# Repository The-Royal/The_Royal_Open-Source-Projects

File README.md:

# The_Royal_Projects
 **A Master Repository For All things Royal Made.**

 From Here forward, all complete, public, and open-sourced projects of my own design will be found here within this repository for consistency and clarity. 

---

 ## Thank You To Everyone for Making these projects possible!

- I’m always down for a nice coffee, beer, or cup of tea. 
- Click my Buymeacoffee link below if you wanted to make a small tip donation <3
- Even just these little donation are so, very much, appreciated.  These really Help me to keep these little projects going and to keep them open source for you guys. 

---

# ***Project Tables:***

## **.01 - Complete Kits**

| *Project* | *Excerpt* | *Main Files for Download* | *Featured Image* |
| --- | --- | :---: | :---: |
| [The Ave.](https://github.com/The-Royal/The_Royal_Open-Source-Projects/tree/master/01%20-%20Complete%20Kits/The_Ave-rev1.2) | A Mighty 50% Battlestation | PCB, Gerbers, Case STLs, RAW CAD |  |
| [LittleFoot](https://github.com/The-Royal/The_Royal_Open-Source-Projects/tree/master/01%20-%20Complete%20Kits/The_Little_Foot-Keyboard-rev2.3) | A Mighty Small, 45% Keyboard  | PCB, Gerbers, Case STLs, RAW CAD |  |
| [RoMac2.1](https://github.com/The-Royal/The_Royal_Open-Source-Projects/tree/master/01%20-%20Complete%20Kits/The_RoMac_rev2.1) | A “Plaid” Keyboard Inspired Macropad | PCB, Gerbers, Acrylic Cover, Diode Tool |  |

## **.02 - PCBs**

| *Project* | *Excerpt* | *Main Files for Download* | *Featured Image* |
| --- | --- | :---: | :---: |
| [Schwann](https://github.com/The-Royal/The_Royal_Open-Source-Projects/tree/schwann/02%20-%20PCBs/Schwann_PCB) | An Ortholinear *"HHKB-Style"* PCB | PCB Gerbers, Plates |  |

## **.03 - Cases**
| *Project* | *Excerpt* | *Main Files for Download* | *Featured Image* |
| --- | --- | :---: | :---: |
| [Minivan 3DP Case](https://github.com/The-Royal/The_Royal_Open-Source-Projects/tree/master/03%20-%20Cases/Minivan%203D%20Printed%20Case) | A Simple Minivan Case | STLs |  |
| [Minivan FR4 Plate Case](https://github.com/The-Royal/The_Royal_Open-Source-Projects/tree/master/03%20-%20Cases/Minivan%20Plate%20Case) | A 2-Part FR4(PCB Material) Plate Case for (rev3+) Minivan PCBs | Gerbers |  |
| [*Vitamins Inc.* Case](https://github.com/The-Royal/The_Royal_Open-Source-Projects/tree/master/03%20-%20Cases/Vitamins-Included_Case-master) | A 3D-Printed Case for the Hotswap Ed. Let's Split Keyboard | Case STLs, Plates |  |

## **.04 - FR4 Plates**
| *Switch Plate* | *Material* | *Main Files for Download* | *Featured Image* |
| --- | --- | :---: | :---: |
| [Minivan FR4 Plates](https://github.com/The-Royal/The_Royal_Open-Source-Projects/tree/master/04%20-%20FR4%20Plates/FR4_Plate-Minivan) | FR4 *(PCB Material)* | Gerbers |  |
| [Roadkit FR4 Plates](https://github.com/The-Royal/The_Royal_Open-Source-Projects/tree/master/04%20-%20FR4%20Plates/FR4_Plate-Roadkit) | FR4 *(PCB Material)* | Gerbers |  |

## **.05 - Other**
| *Project* | *Excerpt* | *Main Files for Download* | *Featured Image* |
| --- | --- | :---: | :---: |
| [Spring Lube Station](https://github.com/The-Royal/The_Royal_Open-Source-Projects/tree/master/05%20-%20Other/Tools-Spring_Lube_Station) | A 3D-Printed Tool For More Consistent Switch-Spring Lubing  | STLs, Sketches |  |
| [Stem-A-Jig](https://github.com/The-Royal/The_Royal_Open-Source-Projects/tree/master/05%20-%20Other/Tools-Stem-a-Jig) | A 3D-Printed Stem Gripper For Hand Lubing Switch Stems **(designed around compliant mechanisms)* | STL, G-Code |  |

---

 ## Thank You *AGAIN* for Making These Projects Possible!

- I’m always down for a nice coffee, beer, or cup of tea. 
- Click my Buymeacoffee link below if you wanted to make a small tip donation <3
- Even just these little donation are so, very much, appreciated.  These really Help me to keep these little projects going and to keep them open source for you guys. 

---

```</end>```

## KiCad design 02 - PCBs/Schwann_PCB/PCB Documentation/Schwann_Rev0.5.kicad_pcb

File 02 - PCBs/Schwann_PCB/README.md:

# The Schwann PCB
## ```Updated Aug. 22, 2020: (rev0.5b) - "Added Dual RESET switch footprints (top/bottom)"```

An ortholinear "HHKB" style PCB.  Specifically designed for use in the [Neuron 40% Keyboard](https://geekhack.org/index.php?topic=102681.0) by Walletburner of Geekhack. 

While not proprietary, the Schwann PCB has cut-off bottom corners and may not be compatible with many, current, after-market cases.  A Custom Designed case will most likely be the correct route. Acrylic is always a solid option.

## **Specs/Features**
- Powered By QMK Firmware (*Soon to be in QMK Configurator)
- Compatible and Designed for use with the Neuron Keyboard Case
- USB Type-C Connection
- x8 Optional WS2812B RGB LEDs
- No In-Switch LED Support
- Expansive Ortholinear Bottom Row Options
- and (IMO) A Beautiful PCB Aesthetically

## [**Non-Official QMK Firmware Documentation Can Be Found Here**](https://github.com/TheRoyalSweatshirt/The_Royal_QMK_Firmware_Vault/tree/master/In-Development_Boards/schwann)

## **Layout Options**

## **Building**
This Repo was realeased to the public so that you can order some of these for yourself and skip the chain! Just upload the gerbers from the latest release section and send them to your favorite PCB Production facility ([JLCPCB](https://jlcpcb.com/) is a fantastic and Cheap Facility), Order the Components Listed below (My Personal Choice is [LCSC](https://lcsc.com/)), and solder up! 

*Thin Liquid Flux, Thin (.6mm Min Diameter) Solder, A Decent Soldering Iron/Station are required for a well function PCB and an intact sanity.

I am not responsible for anything DIY assembly you man do yourself.  This information is public so it is  between you and the PCB to decide who will be the victor.  Assemble safely and assemble confidently my friends!

## **Bill of materials (BOM)**
Amount is for a **SINGLE SCHWANN PCB**.

Multiply as needed for higher quantities.

| LCSC part # | Description   | Value   | Package  | Amount |
| ----------- | ------------- | ------- | -------- | ------:|
| C128353     | Capacitor     | 0.1uF   | 0805     | 3      |
| C215803     | Capacitor     | 1uF     | 0805     | 1      |
| C2099       | Diode         |         | SOD-123  | 48     |
| C20799      | Fuse          |         | 1206     | 1      |
| C165948     | USB Connector |         | SMD/THT  | 1      |
| C103904     | Resistor      | 10K     | 0805     | 2      |
| C147798     | Resistor      | 5.1K    | 0805     | 2      |
| C325772     | Resistor      | 22      | 0805     | 2      |
| C45874      | MCU           | 32U4-AU | QFN-44   | 1      |
| C32180      | Crystal       | 16MHz   | SMD-3213 | 1      |
| C127478     | RST_Switch    |         | SMD      | 1      |

***Optional/Other:**
| LCSC part # | Description   | Value   | Package  | Amount |
| ----------- | ------------- | ------- | -------- | ------:|
| C114585     | WS2812B       | RGB     | 5050     | 8      |

### **Note On Viewing PCB Documentation:*
The latest KiCAD version will be needed to view the PCB Docs.  As well as correct project file path configurations.

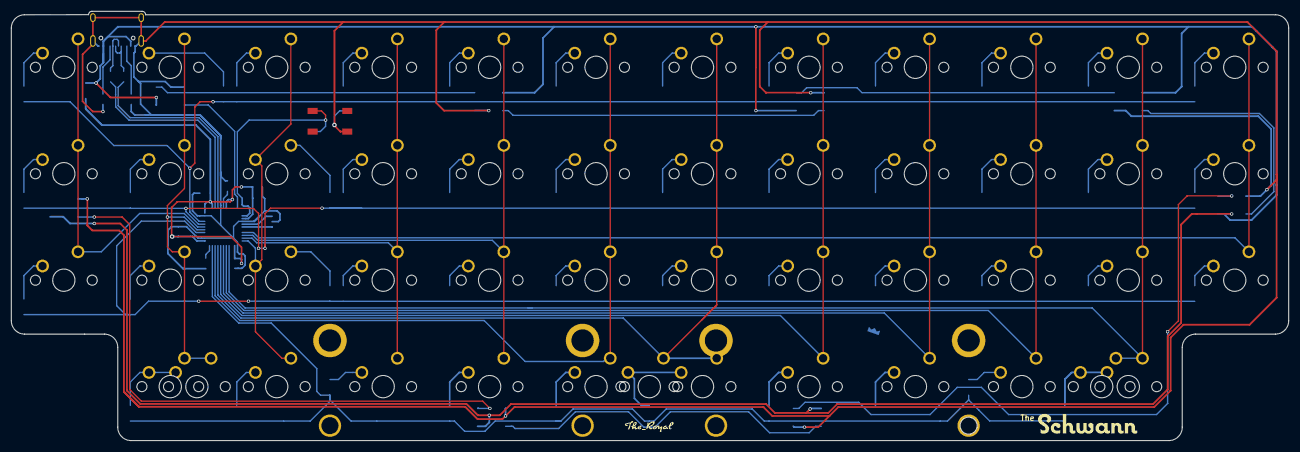
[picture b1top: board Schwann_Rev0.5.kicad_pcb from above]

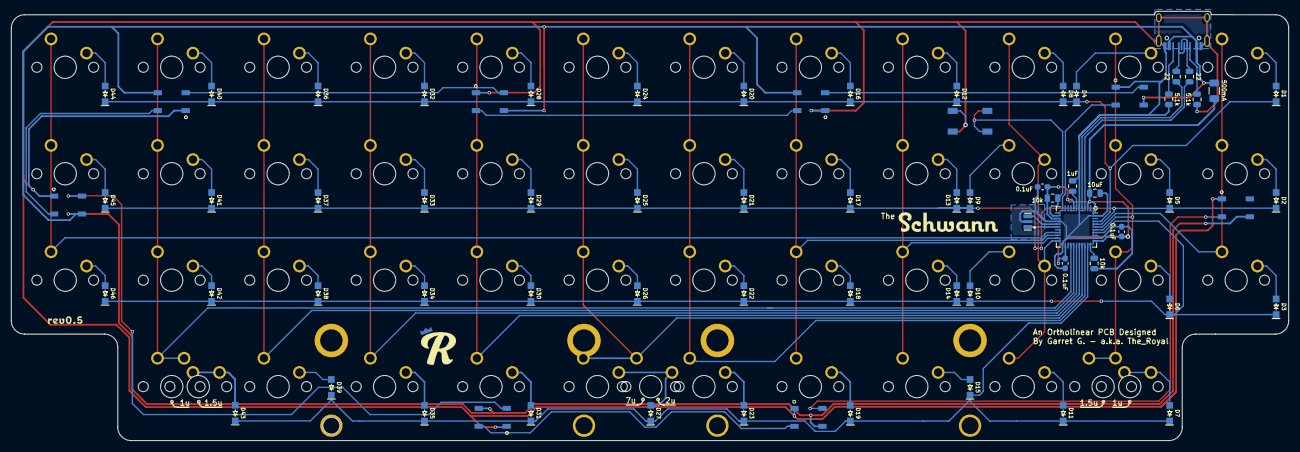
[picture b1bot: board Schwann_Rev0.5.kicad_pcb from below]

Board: 2 copper layers, 228.6 x 76.8 mm, 122 parts (70 on the bottom side), 84 nets.

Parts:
0.1uF, 0.1uF#2, 0.1uF#3: 0.1uF; C_0603_1608Metric_Pad1.05x0.95mm_HandSolder
1uF: 1uF; C_0805_2012Metric
5.1k, 5.1k#2: 5.1k; R_0805_2012Metric
10k, 10k#2: 10k; R_0805_2012Metric
10uF: 10uF; C_0805_2012Metric
22, 22#2: 22; R_0805_2012Metric
500mA: 500mA; Fuse_1206_3216Metric
Cystal1: CSTCE16M0V53-R0; CSTCE-V
D1, D2, D3, D4, D5, D6, D7, D8, D9, D10, D11, D12, D13, D14, D15, D16, D17, D18, D19, D20, D21, D22, D23, D24, D25, D26, D27, D28, D29, D30, D31, D32, D33, D34, D35, D36, D37, D38, D39, D40, D41, D42, D43, D44, D45, D46: D; D_SOD123_Basic
K7u1: KEYSW; MX_PCB_7u_STABONLY
KR2u1: KEYSW; MX_PCB_2u_STABONLY
MCU1: ATmega32U4-AU; QFN-44-1EP_7x7mm_P0.5mm_EP5.2x5.2mm
MX1, MX2, MX3, MX4, MX5, MX6, MX7, MX8, MX9, MX10, MX11, MX12, MX13, MX14, MX15, MX16, MX17, MX18, MX19, MX20, MX21, MX22, MX23, MX24, MX25, MX26, MX27, MX28, MX29, MX30, MX31, MX32, MX33, MX34, MX35, MX36, MX37, MX38, MX39, MX40, MX41, MX42, MX43, MX44, MX45, MX46: MX-NoLED; MX_PCB_100H_SIMPLE_NOSILK
MX1.5uL1, MX1.5uR1: MX-NoLED; MX_PCB_150H
MX_7u1: MX-NoLED; MX_PCB_100H_SIMPLE_NOSILK
RGB1, RGB2, RGB3, RGB4, RGB5, RGB7, RGB8, RGB10: WS2812B
Rst1, Rst1#2: SW_PUSH; SKQG-1155865
USB1: HRO-TYPE-C-31-M-12

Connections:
+5V: 0.1uF.1, 0.1uF#2.1, 0.1uF#3.1, 10k.1, 10uF.1, 500mA.1, MCU1.2, MCU1.7, MCU1.14, MCU1.24, MCU1.34, MCU1.44
D+: 22.2, USB1.6, USB1.8
D-: 22#2.2, USB1.5, USB1.7
GND: 0.1uF.2, 0.1uF#2.2, 0.1uF#3.2, 1uF.2, 5.1k.2, 5.1k#2.2, 10k#2.2, 10uF.2, Cystal1.2, MCU1.5, MCU1.15, MCU1.23, MCU1.35, MCU1.43, RGB1.3, RGB2.3, RGB3.3, RGB4.3, RGB5.3, RGB7.3, RGB8.3, RGB10.3, Rst1.1, Rst1#2.1, USB1.1, USB1.12, USB1.13
unnamed: 1uF.1, MCU1.6
unnamed: Cystal1.1, MCU1.17
unnamed: Cystal1.3, MCU1.16
unnamed: D1.2, MX1.2
unnamed: D2.2, MX13.2
unnamed: D3.2, MX25.2
unnamed: D4.2, MX2.2
unnamed: D5.2, MX14.2
unnamed: D6.2, MX26.2
unnamed: D7.2, MX1.5uL1.2, MX37.2
unnamed: D8.2, MX3.2
unnamed: D9.2, MX15.1
unnamed: D10.2, MX27.1
unnamed: D11.2, MX38.2
unnamed: D12.2, MX4.2
unnamed: D13.2, MX16.2
unnamed: D14.2, MX28.2
unnamed: D15.2, MX39.2
unnamed: D16.2, MX5.2
unnamed: D17.2, MX17.2
unnamed: D18.2, MX29.2
unnamed: D19.2, MX40.2
unnamed: D20.2, MX6.2
unnamed: D21.2, MX18.2
unnamed: D22.2, MX30.2
unnamed: D23.2, MX41.2
unnamed: D24.2, MX7.2
unnamed: D25.2, MX19.2
unnamed: D26.2, MX31.2
unnamed: D27.2, MX42.2, MX_7u1.2
unnamed: D28.2, MX8.2
unnamed: D29.2, MX20.2
unnamed: D30.2, MX32.2
unnamed: D31.2, MX43.2
unnamed: D32.2, MX9.2
unnamed: D33.2, MX21.2
unnamed: D34.2, MX33.2
unnamed: D35.2, MX44.2
unnamed: D36.2, MX10.2
unnamed: D37.2, MX22.2
unnamed: D38.2, MX34.2
unnamed: D39.2, MX45.2
unnamed: D40.2, MX11.2
unnamed: D41.2, MX23.2
unnamed: D42.2, MX35.2
unnamed: D43.2, MX1.5uR1.2, MX46.2
unnamed: D44.2, MX12.2
unnamed: D45.2, MX24.2
unnamed: D46.2, MX36.2
unnamed: 22#2.1, MCU1.3
unnamed: 22.1, MCU1.4
unnamed: 10k.2, MCU1.13, Rst1.2, Rst1#2.2
unnamed: 10k#2.1, MCU1.33
unnamed: 5.1k.1, USB1.10
unnamed: 5.1k#2.1, USB1.4
unnamed: RGB1.2, RGB2.4
unnamed: RGB2.2, RGB3.4
unnamed: RGB3.2, RGB4.4
unnamed: RGB4.2, RGB5.4
unnamed: RGB5.2, RGB7.4
unnamed: RGB7.2, RGB8.4
unnamed: RGB8.2, RGB10.4
RGB: MCU1.11, RGB1.4
VCC: 500mA.2, RGB1.1, RGB2.1, RGB3.1, RGB4.1, RGB5.1, RGB7.1, RGB8.1, RGB10.1, USB1.2, USB1.11
col1: MCU1.39, MX1.1, MX13.1, MX25.1
col2: MCU1.38, MX1.5uL1.1, MX2.1, MX14.1, MX26.1, MX37.1
col3: MCU1.22, MX3.1, MX15.2, MX27.2, MX38.1
col4: MCU1.21, MX4.1, MX16.1, MX28.1, MX39.1
col5: MCU1.20, MX5.1, MX17.1, MX29.1, MX40.1
col6: MCU1.31, MX6.1, MX18.1, MX30.1, MX41.1
col7: MCU1.30, MX7.1, MX19.1, MX31.1, MX42.1, MX_7u1.1
col8: MCU1.29, MX8.1, MX20.1, MX32.1, MX43.1
col9: MCU1.28, MX9.1, MX21.1, MX33.1, MX44.1
col10: MCU1.27, MX10.1, MX22.1, MX34.1, MX45.1
col11: MCU1.26, MX1.5uR1.1, MX11.1, MX23.1, MX35.1, MX46.1
col12: MCU1.19, MX12.1, MX24.1, MX36.1
row1: D1.1, D4.1, D8.1, D12.1, D16.1, D20.1, D24.1, D28.1, D32.1, D36.1, D40.1, D44.1, MCU1.41
row2: D2.1, D5.1, D9.1, D13.1, D17.1, D21.1, D25.1, D29.1, D33.1, D37.1, D41.1, D45.1, MCU1.40
row3: D3.1, D6.1, D10.1, D14.1, D18.1, D22.1, D26.1, D30.1, D34.1, D38.1, D42.1, D46.1, MCU1.37
row4: D7.1, D11.1, D15.1, D19.1, D23.1, D27.1, D31.1, D35.1, D39.1, D43.1, MCU1.32

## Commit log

2020-03-21 Schwann Commit
2020-03-21 Link
2020-03-21 add Romac
2020-03-31 Fix Schwann_Stab Issue
2020-03-31 Update Schwann Fix Gerbers
2020-05-18 Build guide draft and links to more parts
2020-05-18 More edits
2020-05-20 add stem a jig
2020-05-27 These build instructions should work out well for folks not doing something weird
2020-06-02 Final build guide edits
2020-06-02 Fix indentation
2020-08-22 add spring lube station and vitamins inc. case
2020-08-22 add dual reset gerbers to schwann pcb and add plate files
2020-08-22 add data file and schwann layout
2020-08-22 add table to master readme
2020-08-22 update read me, reorder folders add platefolder
2020-08-22 or: you need to resolve your current index first
2020-08-22 update schwann branch
2020-08-22 update schwann master pcb doc
2020-08-22 add kicad directory files
2020-08-22 update schwan files
2020-08-22 add parts library
2020-08-22 update folder structure and schwann plate file readme
2020-08-22 add fr4 plates
2020-08-22 update FR4 doc
2020-08-22 add Minivan FR4 plate Case
2020-08-22 update readmes
2020-08-22 add baseplate pic
2020-08-24 add minivan case folder
2020-08-24 update master table and minivan case readme
2020-11-13 init the_ave stem
2020-11-13 Teach myself english
2021-05-05 Fixed broken link in RoMac-readme
